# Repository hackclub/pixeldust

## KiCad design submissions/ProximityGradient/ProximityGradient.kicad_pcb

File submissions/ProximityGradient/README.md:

---
name: "Youssef Mostafa"
slack_id: "U086LEPFDC5"
github_handle: "@yousseftechdev"
tutorial: [default guide](https://pixeldust.hackclub.com/guidelines)
wokwi: [WOKWI PROJECT](https://wokwi.com/projects/426893863510548481)
---

# ProximityGradient

Wokwi link: [https://wokwi.com/projects/426893863510548481](https://wokwi.com/projects/426893863510548481)

<!-- Uncomment the line below if you need a soldering iron -->
<!-- ⚠️ I would like to [reason for iron], so I would need a soldering iron. -->

Describe your board in 2-3 sentences. What are you making? What will it do? Please add a lot of pictures here!!

**Simple NeoMatrix connected to an UltraSonic distance sensor (Provided by me) that shows a circle that grows in proportion to the distance, the closer and object gets to the sensor, the bigger the circle gets and the red-er it gets.**

A simplified BOM table
(pls include rough pricing of any extra components you're using)

<!-- Example: -->

| Comment           | Footprint                                      | Quantity | LCSC     | Cost   |
|-------------------|------------------------------------------------|----------|----------|--------|
| 100uF             | C_1206_3216Metric_Pad1.33x1.80mm_HandSolder    | 1        | C15008   | 0.0682$|
| 4.7nF             | C_0402_1005Metric_Pad0.74x0.62mm_HandSolder    | 8        | C1538    | 0.0011$|
| 5.1Kohm           | Resistor_SMD:R_1206_3216Metric_Pad1.30x1.75mm_HandSolder| 2        | 0805W8F5101T5E    | $0.0018|
| WS2812B           | LED_WS2812B_PLCC4_5.0x5.0mm_P3.2mm             | 49       | XL-5050RGBC-WS2812B    | $0.0489|
| XIAO-RP2040-DIP   | XIAO-RP2040-DIP                                | 1        |          |

Tell us a little bit about your design process. What were some challenges? What helped?
The biggest challenge I had to face was learning how to use KiCad, thankfully the slack members helped me a lot, I had to change the design a lot because a slack member would point out an error in my board.

Some images of your design (make sure to include both the PCB and Schematic!):

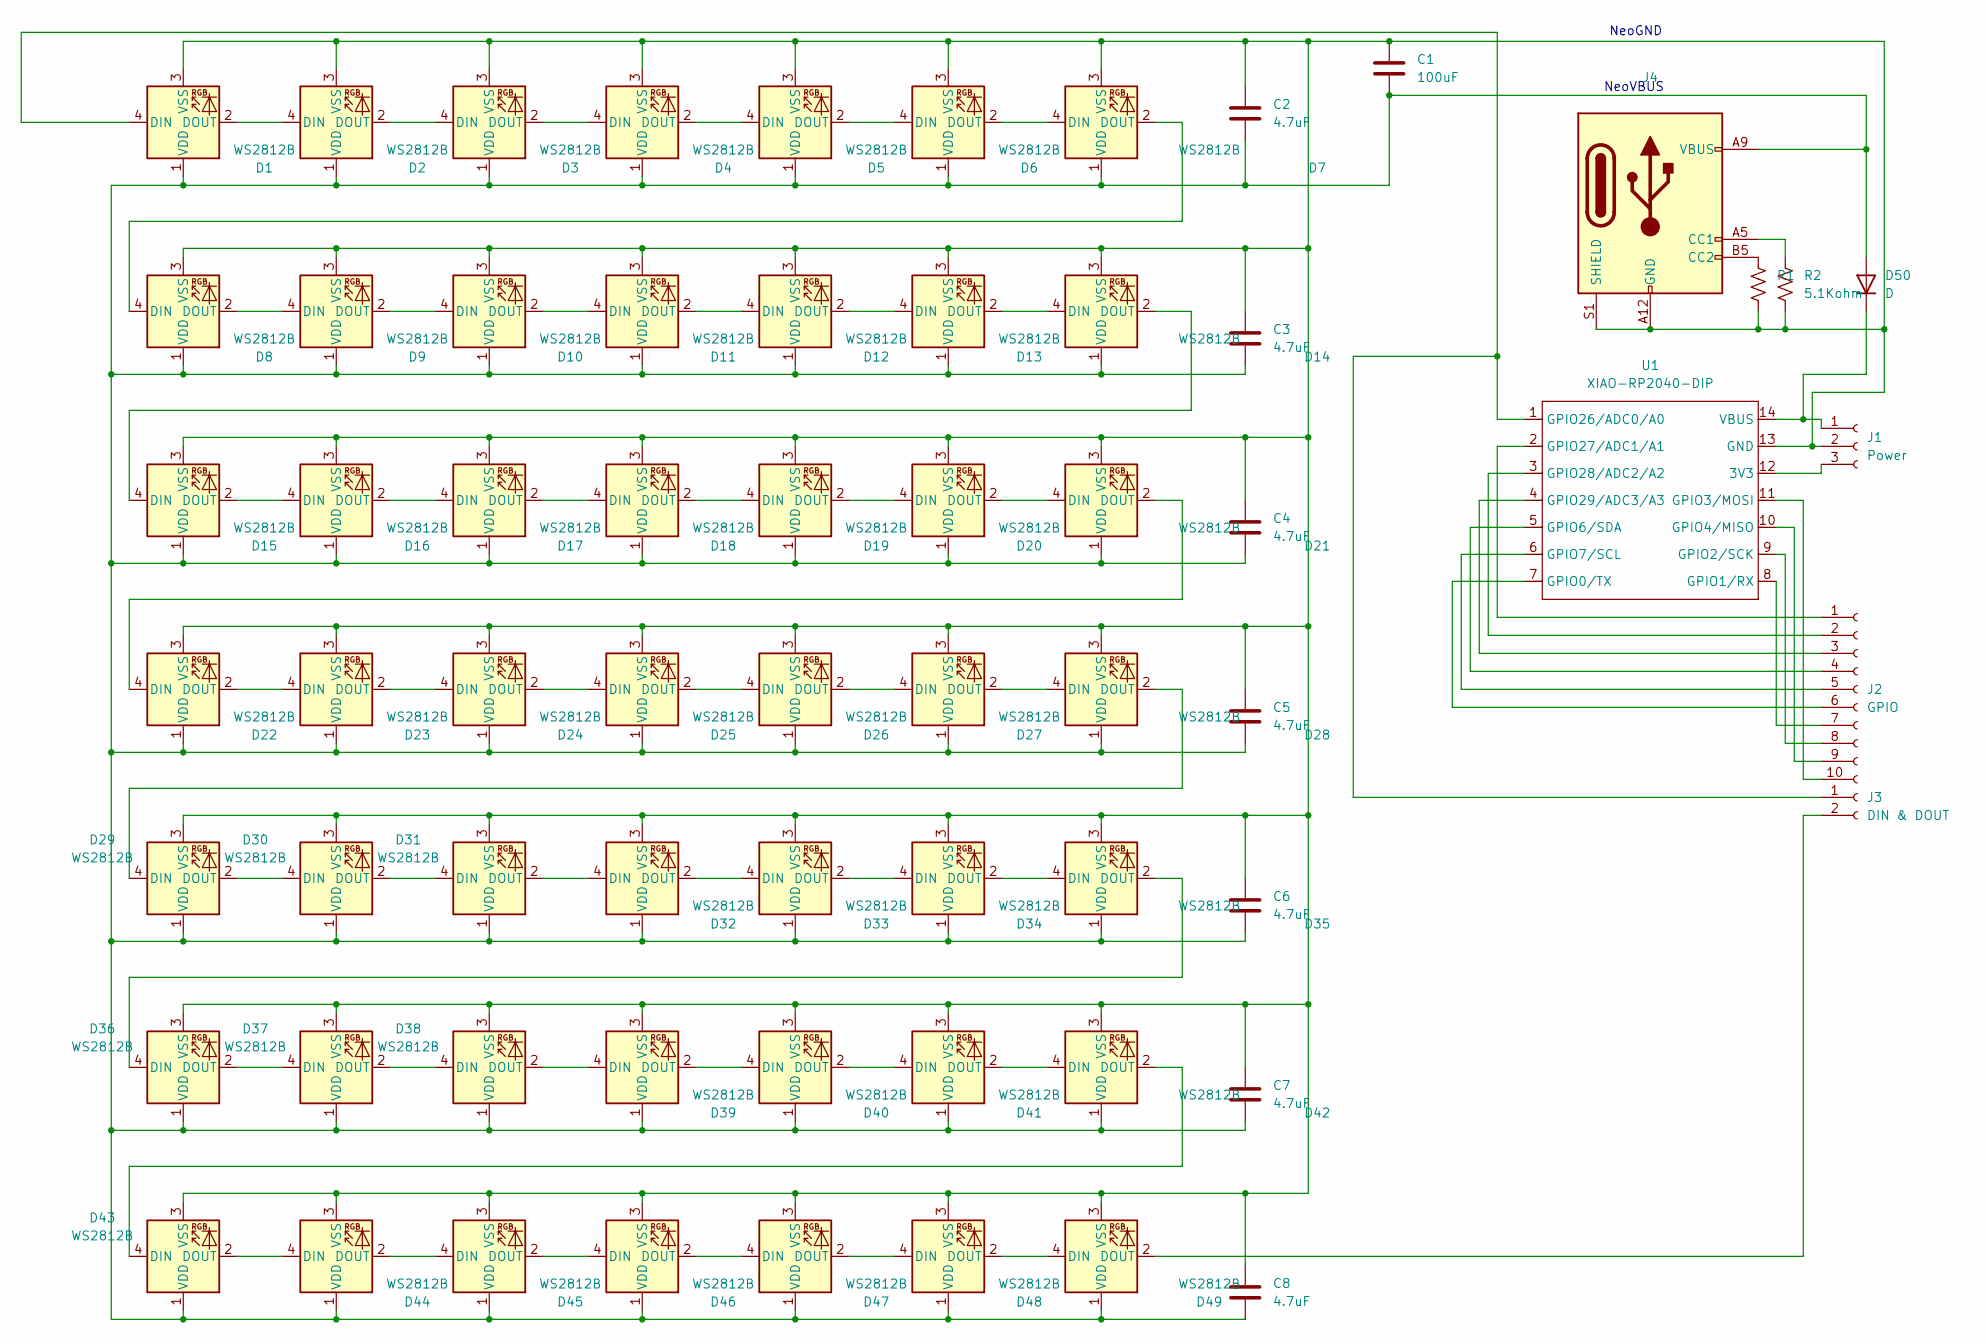
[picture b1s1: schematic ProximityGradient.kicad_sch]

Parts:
C1: 100uF; C_1206_3216Metric_Pad1.33x1.80mm_HandSolder
C2, C3, C4, C5, C6, C7, C8: 4.7uF; C_0805_2012Metric_Pad1.18x1.45mm_HandSolder
D1, D2, D3, D4, D5, D6, D7, D8, D9, D10, D11, D12, D13, D14, D15, D16, D17, D18, D19, D20, D21, D22, D23, D24, D25, D26, D27, D28, D29, D30, D31, D32, D33, D34, D35, D36, D37, D38, D39, D40, D41, D42, D43, D44, D45, D46, D47, D48, D49: WS2812B; LED_WS2812B_PLCC4_5.0x5.0mm_P3.2mm
D50: D; D_0805_2012Metric_Pad1.15x1.40mm_HandSolder
J1: Power; PinSocket_1x03_P2.00mm_Vertical
J2: GPIO; PinSocket_1x10_P2.00mm_Vertical
J3: DIN & DOUT; PinSocket_1x02_P2.00mm_Vertical
J4: USB_C_Receptacle_PowerOnly_6P; USB_C_Receptacle_GCT_USB4125-xx-x_6P_TopMnt_Horizontal
R1: R_US; R_1206_3216Metric_Pad1.30x1.75mm_HandSolder
R2: 5.1Kohm; R_1206_3216Metric_Pad1.30x1.75mm_HandSolder
U1: XIAO-RP2040-DIP

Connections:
unnamed: D1.4 (DIN), J3.1, U1.1 (GPIO26/ADC0/A0)
unnamed: D1.2 (DOUT), D2.4 (DIN)
unnamed: C1.2, C2.2, C3.2, C4.2, C5.2, C6.2, C7.2, C8.2, D1.1 (VDD), D2.1 (VDD), D3.1 (VDD), D4.1 (VDD), D5.1 (VDD), D6.1 (VDD), D7.1 (VDD), D8.1 (VDD), D9.1 (VDD), D10.1 (VDD), D11.1 (VDD), D12.1 (VDD), D13.1 (VDD), D14.1 (VDD), D15.1 (VDD), D16.1 (VDD), D17.1 (VDD), D18.1 (VDD), D19.1 (VDD), D20.1 (VDD), D21.1 (VDD), D22.1 (VDD), D23.1 (VDD), D24.1 (VDD), D25.1 (VDD), D26.1 (VDD), D27.1 (VDD), D28.1 (VDD), D29.1 (VDD), D30.1 (VDD), D31.1 (VDD), D32.1 (VDD), D33.1 (VDD), D34.1 (VDD), D35.1 (VDD), D36.1 (VDD), D37.1 (VDD), D38.1 (VDD), D39.1 (VDD), D40.1 (VDD), D41.1 (VDD), D42.1 (VDD), D43.1 (VDD), D44.1 (VDD), D45.1 (VDD), D46.1 (VDD), D47.1 (VDD), D48.1 (VDD), D49.1 (VDD), D50.2 (A), J4.A9 (VBUS), J4.B9 (VBUS)
unnamed: C1.1, C2.1, C3.1, C4.1, C5.1, C6.1, C7.1, C8.1, D1.3 (VSS), D2.3 (VSS), D3.3 (VSS), D4.3 (VSS), D5.3 (VSS), D6.3 (VSS), D7.3 (VSS), D8.3 (VSS), D9.3 (VSS), D10.3 (VSS), D11.3 (VSS), D12.3 (VSS), D13.3 (VSS), D14.3 (VSS), D15.3 (VSS), D16.3 (VSS), D17.3 (VSS), D18.3 (VSS), D19.3 (VSS), D20.3 (VSS), D21.3 (VSS), D22.3 (VSS), D23.3 (VSS), D24.3 (VSS), D25.3 (VSS), D26.3 (VSS), D27.3 (VSS), D28.3 (VSS), D29.3 (VSS), D30.3 (VSS), D31.3 (VSS), D32.3 (VSS), D33.3 (VSS), D34.3 (VSS), D35.3 (VSS), D36.3 (VSS), D37.3 (VSS), D38.3 (VSS), D39.3 (VSS), D40.3 (VSS), D41.3 (VSS), D42.3 (VSS), D43.3 (VSS), D44.3 (VSS), D45.3 (VSS), D46.3 (VSS), D47.3 (VSS), D48.3 (VSS), D49.3 (VSS), J1.2, J4.A12 (GND), J4.B12 (GND), J4.S1 (SHIELD), R1.2, R2.2, U1.13 (GND)
unnamed: D2.2 (DOUT), D3.4 (DIN)
unnamed: D3.2 (DOUT), D4.4 (DIN)
unnamed: D4.2 (DOUT), D5.4 (DIN)
unnamed: D5.2 (DOUT), D6.4 (DIN)
unnamed: D6.2 (DOUT), D7.4 (DIN)
unnamed: D7.2 (DOUT), D8.4 (DIN)
unnamed: D8.2 (DOUT), D9.4 (DIN)
unnamed: D9.2 (DOUT), D10.4 (DIN)
unnamed: D10.2 (DOUT), D11.4 (DIN)
unnamed: D11.2 (DOUT), D12.4 (DIN)
unnamed: D12.2 (DOUT), D13.4 (DIN)
unnamed: D13.2 (DOUT), D14.4 (DIN)
unnamed: D14.2 (DOUT), D15.4 (DIN)
unnamed: D15.2 (DOUT), D16.4 (DIN)
unnamed: D16.2 (DOUT), D17.4 (DIN)
unnamed: D17.2 (DOUT), D18.4 (DIN)
unnamed: D18.2 (DOUT), D19.4 (DIN)
unnamed: D19.2 (DOUT), D20.4 (DIN)
unnamed: D20.2 (DOUT), D21.4 (DIN)
unnamed: D21.2 (DOUT), D22.4 (DIN)
unnamed: D22.2 (DOUT), D23.4 (DIN)
unnamed: D23.2 (DOUT), D24.4 (DIN)
unnamed: D24.2 (DOUT), D25.4 (DIN)
unnamed: D25.2 (DOUT), D26.4 (DIN)
unnamed: D26.2 (DOUT), D27.4 (DIN)
unnamed: D27.2 (DOUT), D28.4 (DIN)
unnamed: D28.2 (DOUT), D29.4 (DIN)
unnamed: D29.2 (DOUT), D30.4 (DIN)
unnamed: D30.2 (DOUT), D31.4 (DIN)
unnamed: D31.2 (DOUT), D32.4 (DIN)
unnamed: D32.2 (DOUT), D33.4 (DIN)
unnamed: D33.2 (DOUT), D34.4 (DIN)
unnamed: D34.2 (DOUT), D35.4 (DIN)
unnamed: D35.2 (DOUT), D36.4 (DIN)
unnamed: D36.2 (DOUT), D37.4 (DIN)
unnamed: D37.2 (DOUT), D38.4 (DIN)
unnamed: D38.2 (DOUT), D39.4 (DIN)
unnamed: D39.2 (DOUT), D40.4 (DIN)
unnamed: D40.2 (DOUT), D41.4 (DIN)
unnamed: D41.2 (DOUT), D42.4 (DIN)
unnamed: D42.2 (DOUT), D43.4 (DIN)
unnamed: D43.2 (DOUT), D44.4 (DIN)
unnamed: D44.2 (DOUT), D45.4 (DIN)
unnamed: D45.2 (DOUT), D46.4 (DIN)
unnamed: D46.2 (DOUT), D47.4 (DIN)
unnamed: D47.2 (DOUT), D48.4 (DIN)
unnamed: D48.2 (DOUT), D49.4 (DIN)
unnamed: D49.2 (DOUT), J3.2
unnamed: D50.1 (K), J1.1, U1.14 (VBUS)
unnamed: J1.3, U1.12 (3V3)
unnamed: J2.1, U1.2 (GPIO27/ADC1/A1)
unnamed: J2.2, U1.3 (GPIO28/ADC2/A2)
unnamed: J2.3, U1.4 (GPIO29/ADC3/A3)
unnamed: J2.4, U1.5 (GPIO6/SDA)
unnamed: J2.5, U1.6 (GPIO7/SCL)
unnamed: J2.6, U1.7 (GPIO0/TX)
unnamed: J2.7, U1.8 (GPIO1/RX)
unnamed: J2.8, U1.9 (GPIO2/SCK)
unnamed: J2.9, U1.10 (GPIO4/MISO)
unnamed: J2.10, U1.11 (GPIO3/MOSI)
unnamed: J4.A5 (CC1), R2.1
unnamed: J4.B5 (CC2), R1.1

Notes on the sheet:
NeoVBUS
NeoGND

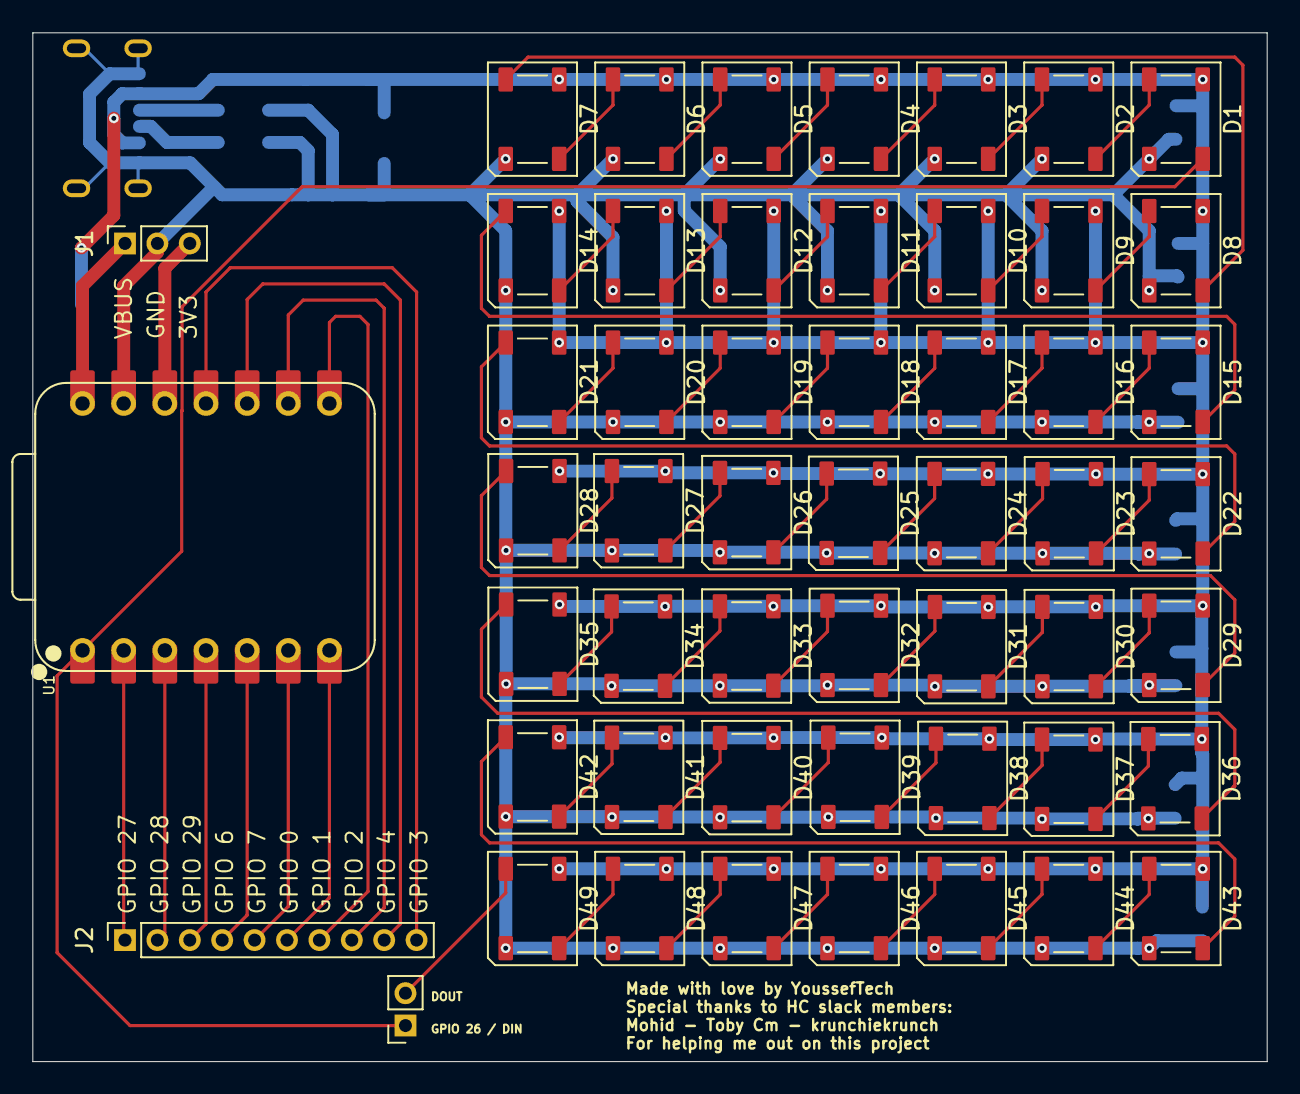
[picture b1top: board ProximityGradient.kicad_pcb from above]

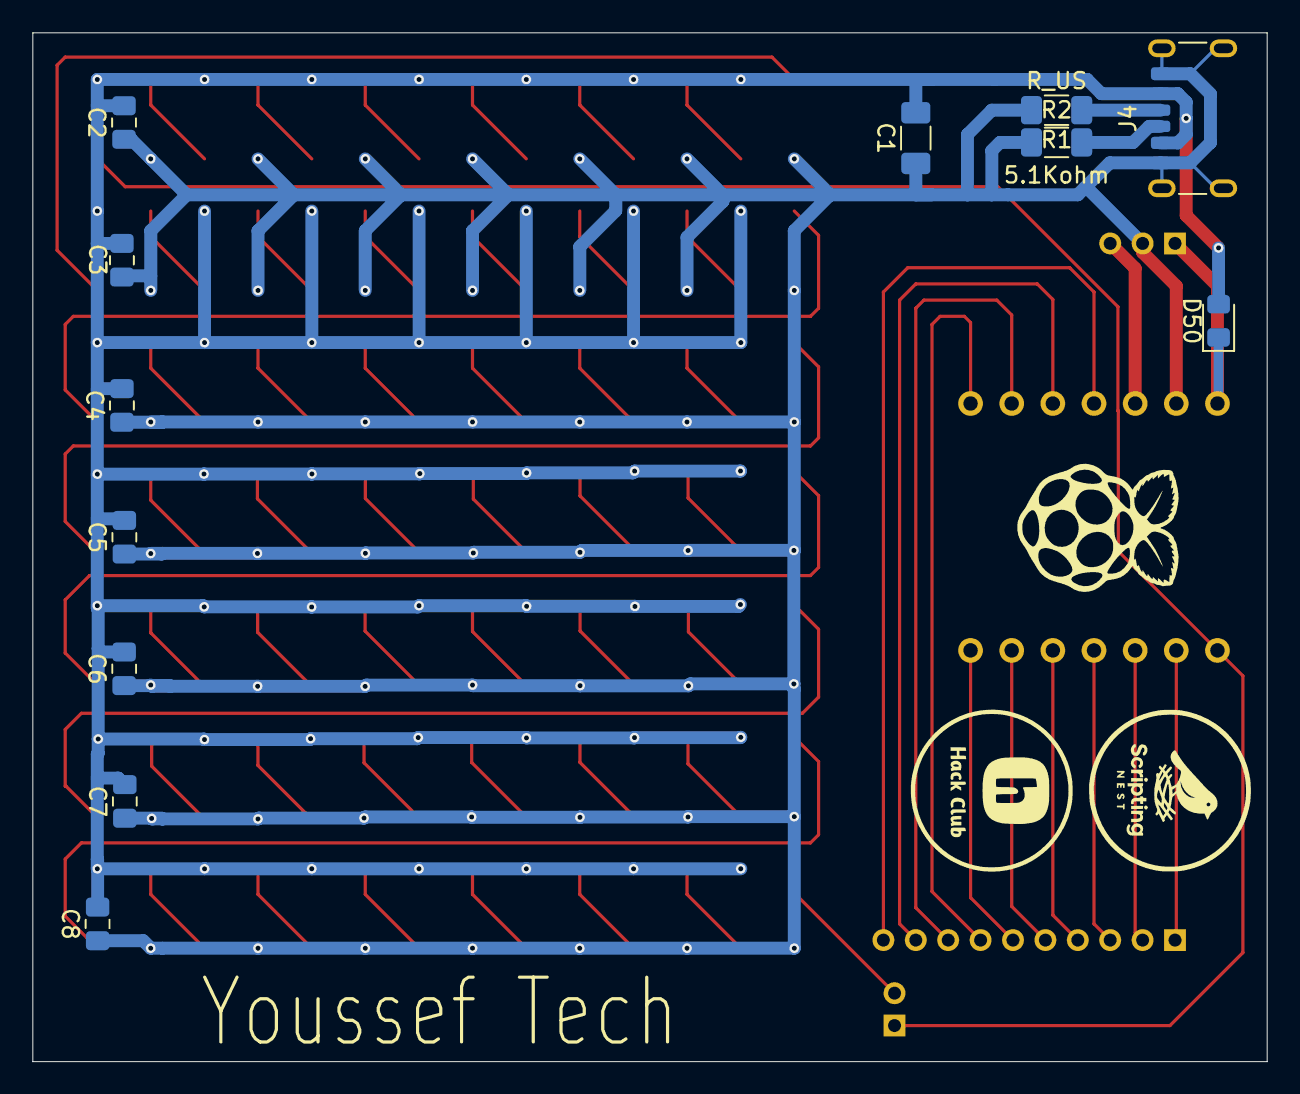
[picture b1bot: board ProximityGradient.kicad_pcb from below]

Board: 2 copper layers, 76.2 x 63.5 mm, 65 parts (12 on the bottom side), 66 nets.

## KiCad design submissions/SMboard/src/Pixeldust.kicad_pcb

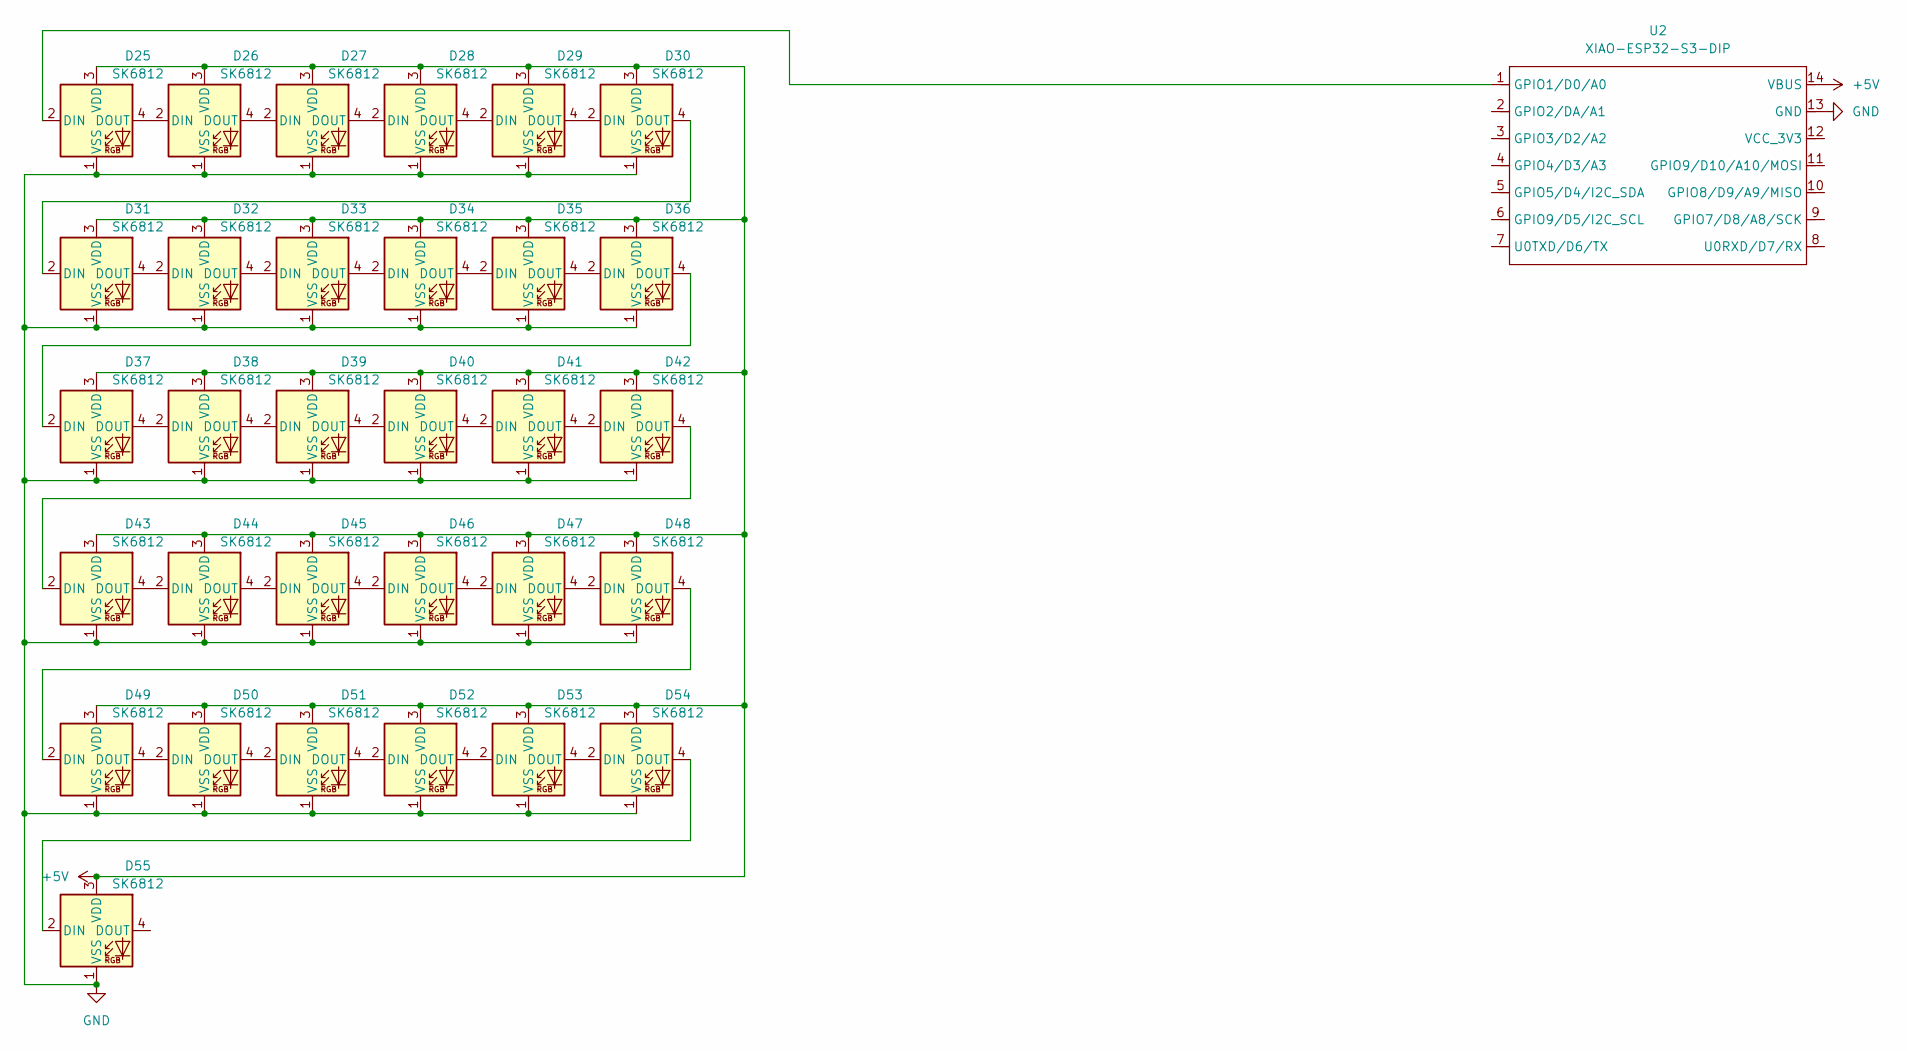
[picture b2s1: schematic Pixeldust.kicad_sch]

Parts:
D25, D26, D27, D28, D29, D30, D31, D32, D33, D34, D35, D36, D37, D38, D39, D40, D41, D42, D43, D44, D45, D46, D47, D48, D49, D50, D51, D52, D53, D54, D55: SK6812; LED_SK6812_PLCC4_5.0x5.0mm_P3.2mm
U2: XIAO-ESP32-S3-DIP; XIAO-ESP32S3-DIP

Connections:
+5V: D25.3 (VDD), D26.3 (VDD), D27.3 (VDD), D28.3 (VDD), D29.3 (VDD), D30.3 (VDD), D31.3 (VDD), D32.3 (VDD), D33.3 (VDD), D34.3 (VDD), D35.3 (VDD), D36.3 (VDD), D37.3 (VDD), D38.3 (VDD), D39.3 (VDD), D40.3 (VDD), D41.3 (VDD), D42.3 (VDD), D43.3 (VDD), D44.3 (VDD), D45.3 (VDD), D46.3 (VDD), D47.3 (VDD), D48.3 (VDD), D49.3 (VDD), D50.3 (VDD), D51.3 (VDD), D52.3 (VDD), D53.3 (VDD), D54.3 (VDD), D55.3 (VDD), U2.14 (VBUS)
GND: D25.1 (VSS), D26.1 (VSS), D27.1 (VSS), D28.1 (VSS), D29.1 (VSS), D30.1 (VSS), D31.1 (VSS), D32.1 (VSS), D33.1 (VSS), D34.1 (VSS), D35.1 (VSS), D36.1 (VSS), D37.1 (VSS), D38.1 (VSS), D39.1 (VSS), D40.1 (VSS), D41.1 (VSS), D42.1 (VSS), D43.1 (VSS), D44.1 (VSS), D45.1 (VSS), D46.1 (VSS), D47.1 (VSS), D48.1 (VSS), D49.1 (VSS), D50.1 (VSS), D51.1 (VSS), D52.1 (VSS), D53.1 (VSS), D54.1 (VSS), D55.1 (VSS), U2.13 (GND)
unnamed: D25.2 (DIN), U2.1 (GPIO1/D0/A0)
unnamed: D25.4 (DOUT), D26.2 (DIN)
unnamed: D26.4 (DOUT), D27.2 (DIN)
unnamed: D27.4 (DOUT), D28.2 (DIN)
unnamed: D28.4 (DOUT), D29.2 (DIN)
unnamed: D29.4 (DOUT), D30.2 (DIN)
unnamed: D30.4 (DOUT), D31.2 (DIN)
unnamed: D31.4 (DOUT), D32.2 (DIN)
unnamed: D32.4 (DOUT), D33.2 (DIN)
unnamed: D33.4 (DOUT), D34.2 (DIN)
unnamed: D34.4 (DOUT), D35.2 (DIN)
unnamed: D35.4 (DOUT), D36.2 (DIN)
unnamed: D36.4 (DOUT), D37.2 (DIN)
unnamed: D37.4 (DOUT), D38.2 (DIN)
unnamed: D38.4 (DOUT), D39.2 (DIN)
unnamed: D39.4 (DOUT), D40.2 (DIN)
unnamed: D40.4 (DOUT), D41.2 (DIN)
unnamed: D41.4 (DOUT), D42.2 (DIN)
unnamed: D42.4 (DOUT), D43.2 (DIN)
unnamed: D43.4 (DOUT), D44.2 (DIN)
unnamed: D44.4 (DOUT), D45.2 (DIN)
unnamed: D45.4 (DOUT), D46.2 (DIN)
unnamed: D46.4 (DOUT), D47.2 (DIN)
unnamed: D47.4 (DOUT), D48.2 (DIN)
unnamed: D48.4 (DOUT), D49.2 (DIN)
unnamed: D49.4 (DOUT), D50.2 (DIN)
unnamed: D50.4 (DOUT), D51.2 (DIN)
unnamed: D51.4 (DOUT), D52.2 (DIN)
unnamed: D52.4 (DOUT), D53.2 (DIN)
unnamed: D53.4 (DOUT), D54.2 (DIN)
unnamed: D54.4 (DOUT), D55.2 (DIN)

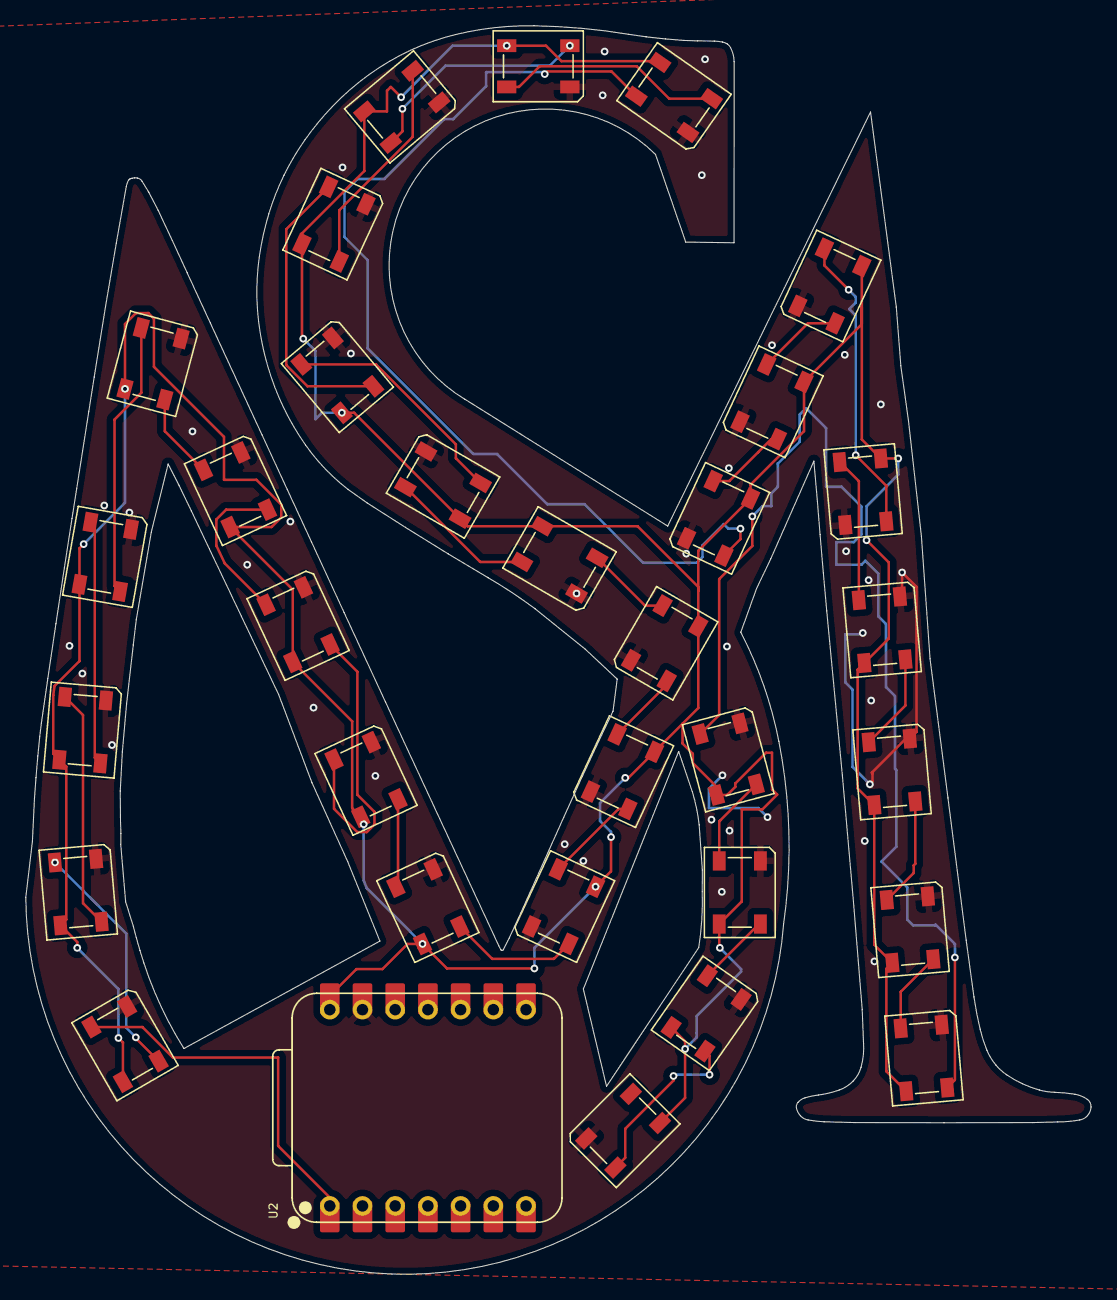
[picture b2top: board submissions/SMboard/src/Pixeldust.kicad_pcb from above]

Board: 2 copper layers, 82.7 x 96.9 mm, 32 parts (0 on the bottom side), 33 nets.

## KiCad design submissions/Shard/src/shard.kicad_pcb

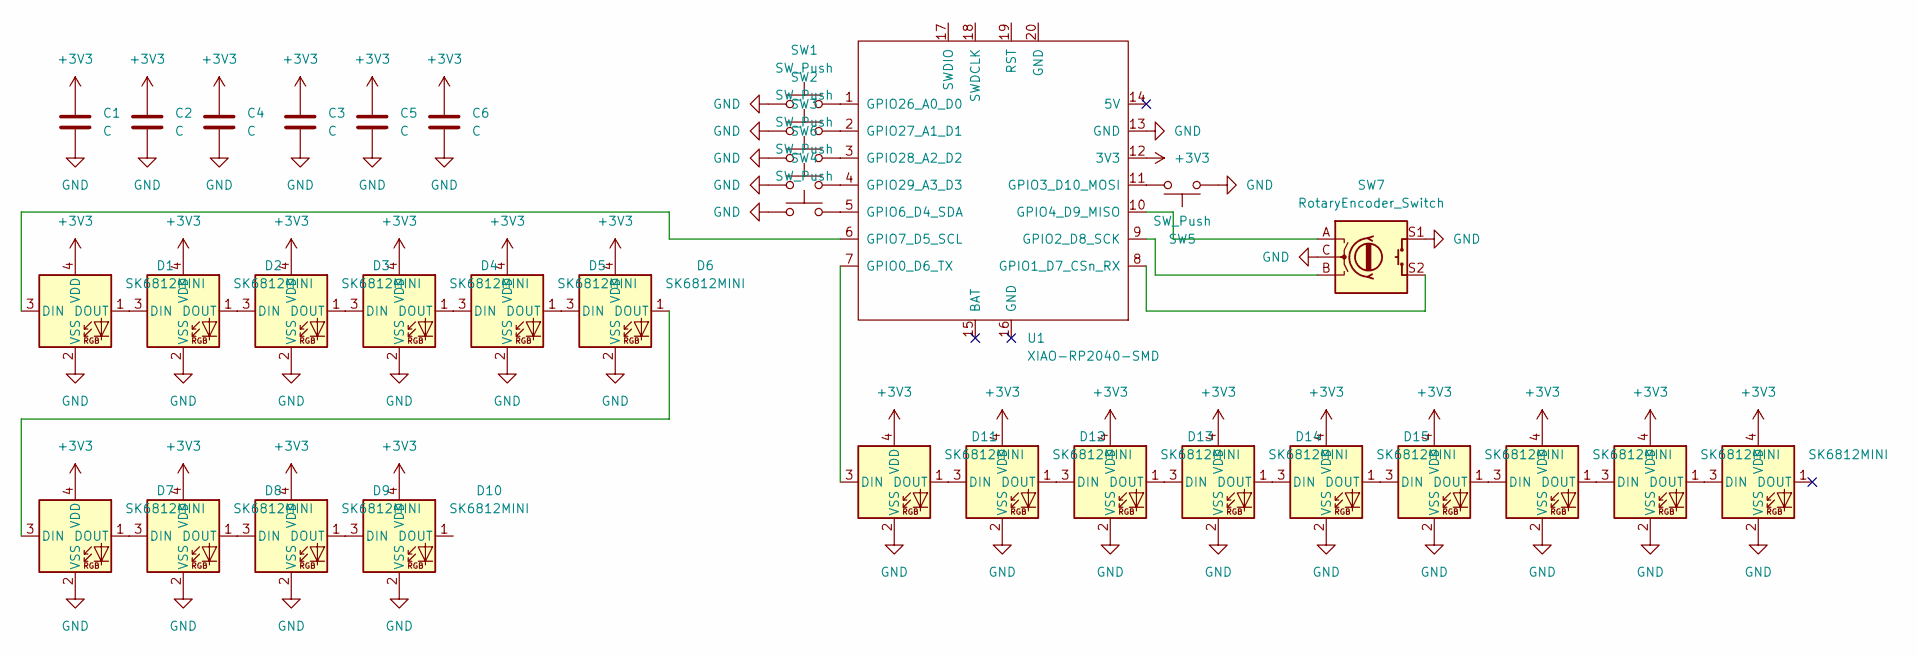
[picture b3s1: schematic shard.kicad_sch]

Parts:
C1, C2, C3, C4, C5, C6: C; C_0805_2012Metric_Pad1.18x1.45mm_HandSolder
D1, D2, D3, D4, D5, D6, D7, D8, D9, D10, D11, D12, D13, D14, D15, D16, D17, D18, D19: SK6812MINI; SK6812MINI-E
SW1, SW2, SW3, SW4, SW5, SW6: SW_Push; SW_Cherry_MX_1.00u_PCB
SW7: RotaryEncoder_Switch; RotaryEncoder_Alps_EC11E-Switch_Vertical_H20mm_MountingHoles
U1: XIAO-RP2040-SMD

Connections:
+3V3: C1.1, C2.1, C3.1, C4.1, C5.1, C6.1, D1.4 (VDD), D2.4 (VDD), D3.4 (VDD), D4.4 (VDD), D5.4 (VDD), D6.4 (VDD), D7.4 (VDD), D8.4 (VDD), D9.4 (VDD), D10.4 (VDD), D11.4 (VDD), D12.4 (VDD), D13.4 (VDD), D14.4 (VDD), D15.4 (VDD), D16.4 (VDD), D17.4 (VDD), D18.4 (VDD), D19.4 (VDD), U1.12 (3V3)
GND: C1.2, C2.2, C3.2, C4.2, C5.2, C6.2, D1.2 (VSS), D2.2 (VSS), D3.2 (VSS), D4.2 (VSS), D5.2 (VSS), D6.2 (VSS), D7.2 (VSS), D8.2 (VSS), D9.2 (VSS), D10.2 (VSS), D11.2 (VSS), D12.2 (VSS), D13.2 (VSS), D14.2 (VSS), D15.2 (VSS), D16.2 (VSS), D17.2 (VSS), D18.2 (VSS), D19.2 (VSS), SW1.1, SW2.1, SW3.1, SW4.1, SW5.2, SW6.2, SW7.C, SW7.S1, U1.13 (GND)
unnamed: D1.3 (DIN), U1.6 (GPIO7_D5_SCL)
unnamed: D1.1 (DOUT), D2.3 (DIN)
unnamed: D2.1 (DOUT), D3.3 (DIN)
unnamed: D3.1 (DOUT), D4.3 (DIN)
unnamed: D4.1 (DOUT), D5.3 (DIN)
unnamed: D5.1 (DOUT), D6.3 (DIN)
unnamed: D6.1 (DOUT), D7.3 (DIN)
unnamed: D7.1 (DOUT), D8.3 (DIN)
unnamed: D8.1 (DOUT), D9.3 (DIN)
unnamed: D9.1 (DOUT), D10.3 (DIN)
unnamed: D11.3 (DIN), U1.7 (GPIO0_D6_TX)
unnamed: D11.1 (DOUT), D12.3 (DIN)
unnamed: D12.1 (DOUT), D13.3 (DIN)
unnamed: D13.1 (DOUT), D14.3 (DIN)
unnamed: D14.1 (DOUT), D15.3 (DIN)
unnamed: D15.1 (DOUT), D16.3 (DIN)
unnamed: D16.1 (DOUT), D17.3 (DIN)
unnamed: D17.1 (DOUT), D18.3 (DIN)
unnamed: D18.1 (DOUT), D19.3 (DIN)
unnamed: SW7.S2, U1.8 (GPIO1_D7_CSn_RX)
unnamed: SW7.B, U1.9 (GPIO2_D8_SCK)
unnamed: SW5.1, U1.11 (GPIO3_D10_MOSI)
unnamed: SW7.A, U1.10 (GPIO4_D9_MISO)
unnamed: SW4.2, U1.5 (GPIO6_D4_SDA)
unnamed: SW1.2, U1.1 (GPIO26_A0_D0)
unnamed: SW2.2, U1.2 (GPIO27_A1_D1)
unnamed: SW3.2, U1.3 (GPIO28_A2_D2)
unnamed: SW6.1, U1.4 (GPIO29_A3_D3)

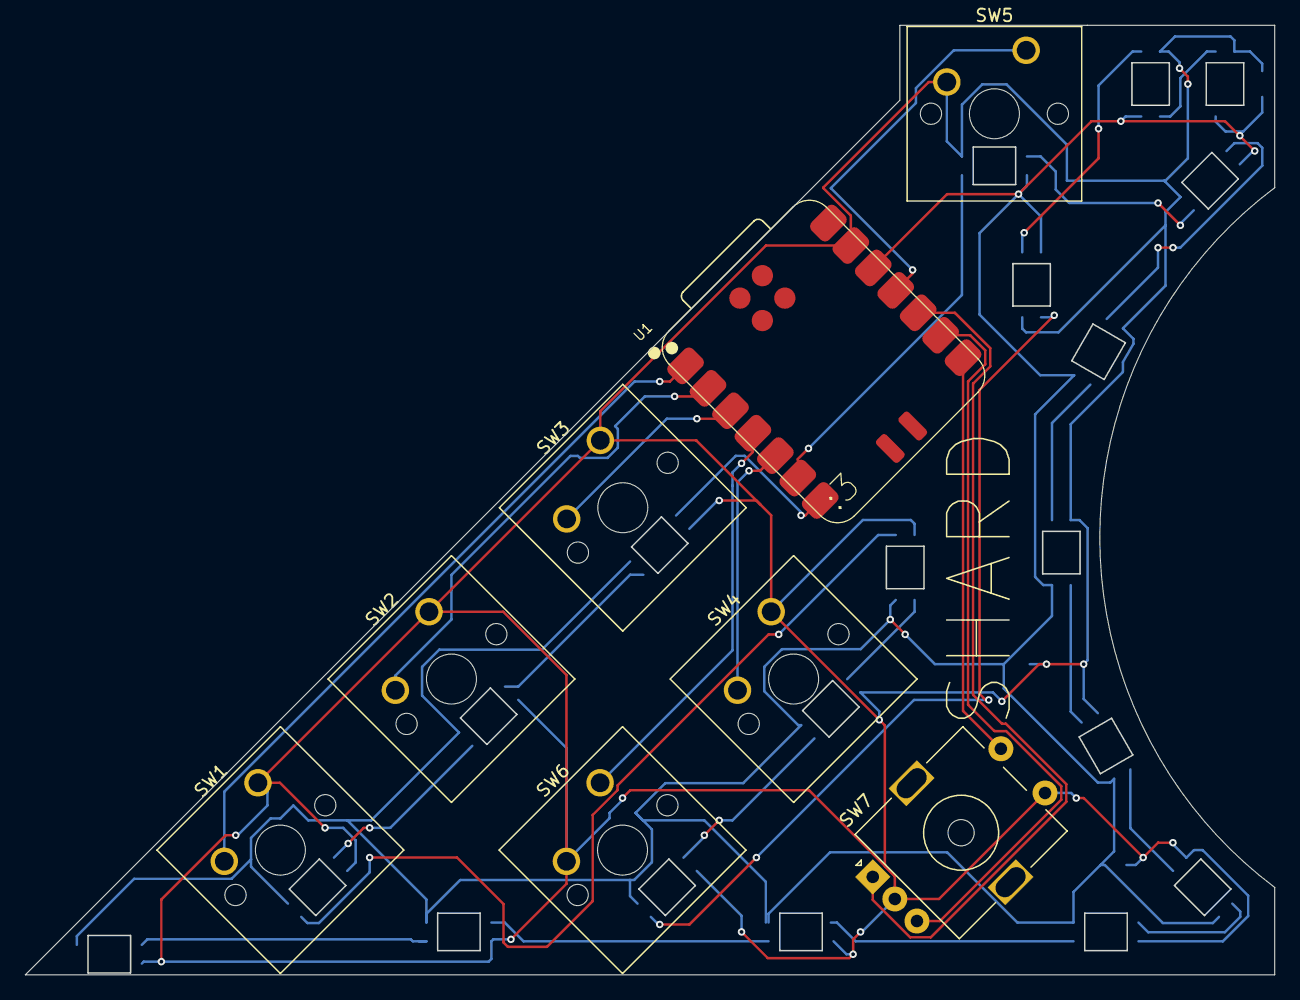
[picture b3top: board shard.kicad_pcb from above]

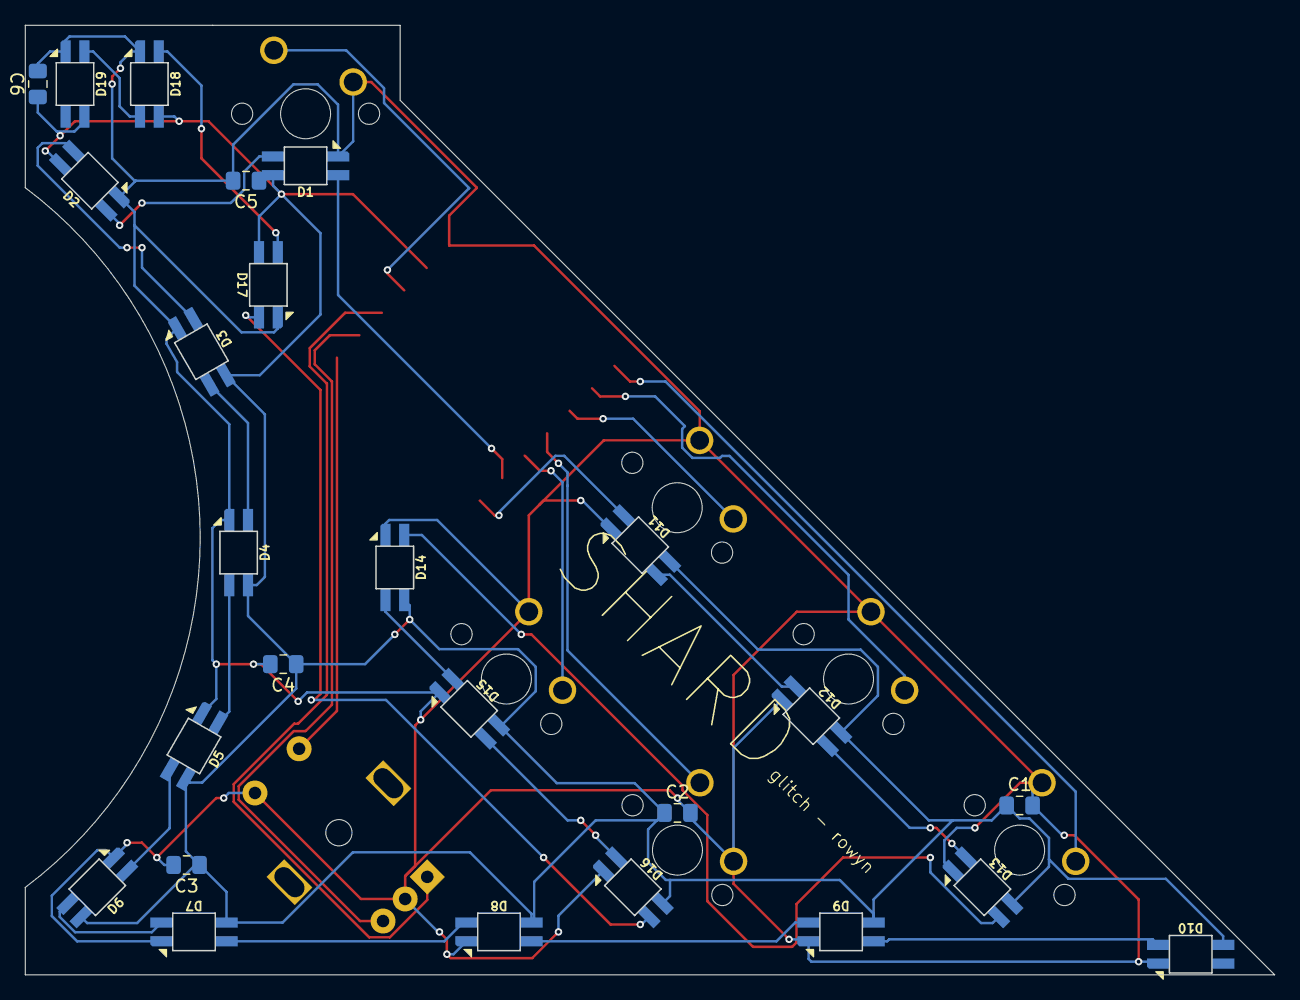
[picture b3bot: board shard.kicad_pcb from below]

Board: 2 copper layers, 100.0 x 76.0 mm, 33 parts (25 on the bottom side), 30 nets.

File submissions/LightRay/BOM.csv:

"Reference","Value","Footprint","Datasheet","Qty","DNP","Exclude from BOM","Exclude from Board"
"C1","100uF","Capacitor_SMD:C_1210_3225Metric_Pad1.33x2.70mm_HandSolder","~","1","","",""
"C2,C3,C4","4.7nF","Capacitor_SMD:C_1206_3216Metric_Pad1.33x1.80mm_HandSolder","~","3","","",""
"D1,D2,D3,D4,D5,D6,D7,D8,D9,D10,D11,D12,D13,D14,D15","WS2812B","LED_SMD:LED_WS2812B_PLCC4_5.0x5.0mm_P3.2mm","https://cdn-shop.adafruit.com/datasheets/WS2812B.pdf","15","","",""
"SW1","RotaryEncoder_Switch","Rotary_Encoder:RotaryEncoder_Alps_EC11E-Switch_Vertical_H20mm","~","1","","",""
"SW2,SW3","SW_Push","Button_Switch_Keyboard:SW_Cherry_MX_1.00u_PCB","~","2","","",""
"U1","XIAO-RP2040-SMD","OPL:XIAO-RP2040-SMD","","1","","",""

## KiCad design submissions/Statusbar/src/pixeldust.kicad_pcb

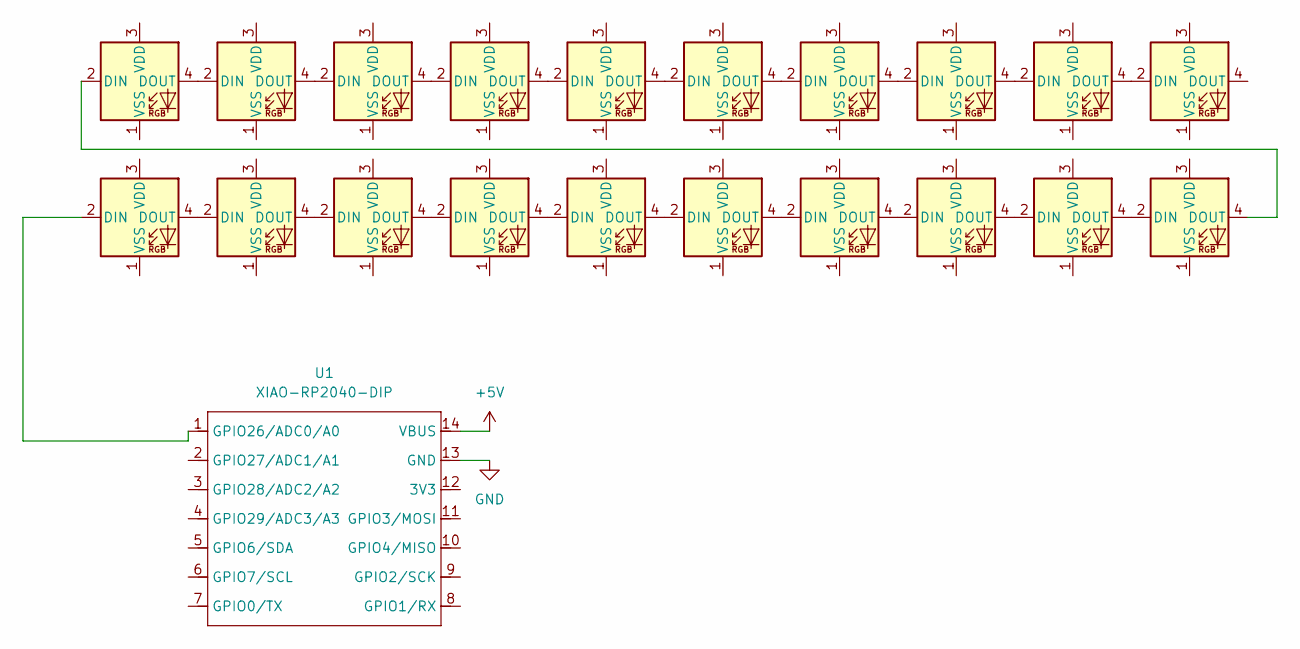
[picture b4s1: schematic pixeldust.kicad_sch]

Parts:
D1, D2, D3, D4, D5, D6, D7, D8, D9, D10, D11, D12, D13, D14, D15, D16, D17, D18, D19, D20: SK6812; LED_SK6812_PLCC4_5.0x5.0mm_P3.2mm
U1: XIAO-RP2040-DIP

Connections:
+5V: U1.14 (VBUS)
GND: U1.13 (GND)
unnamed: D1.2 (DIN), U1.1 (GPIO26/ADC0/A0)
unnamed: D1.4 (DOUT), D2.2 (DIN)
unnamed: D2.4 (DOUT), D3.2 (DIN)
unnamed: D3.4 (DOUT), D4.2 (DIN)
unnamed: D4.4 (DOUT), D5.2 (DIN)
unnamed: D5.4 (DOUT), D6.2 (DIN)
unnamed: D6.4 (DOUT), D7.2 (DIN)
unnamed: D7.4 (DOUT), D8.2 (DIN)
unnamed: D8.4 (DOUT), D9.2 (DIN)
unnamed: D9.4 (DOUT), D10.2 (DIN)
unnamed: D10.4 (DOUT), D11.2 (DIN)
unnamed: D11.4 (DOUT), D12.2 (DIN)
unnamed: D12.4 (DOUT), D13.2 (DIN)
unnamed: D13.4 (DOUT), D14.2 (DIN)
unnamed: D14.4 (DOUT), D15.2 (DIN)
unnamed: D15.4 (DOUT), D16.2 (DIN)
unnamed: D16.4 (DOUT), D17.2 (DIN)
unnamed: D17.4 (DOUT), D18.2 (DIN)
unnamed: D18.4 (DOUT), D19.2 (DIN)
unnamed: D19.4 (DOUT), D20.2 (DIN)

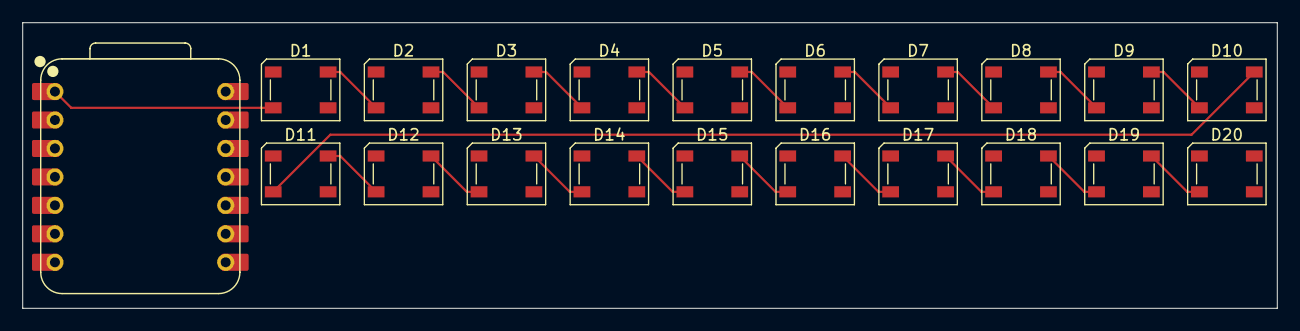
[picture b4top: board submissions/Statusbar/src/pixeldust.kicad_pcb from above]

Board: 2 copper layers, 112.0 x 25.5 mm, 21 parts (0 on the bottom side), 20 nets.

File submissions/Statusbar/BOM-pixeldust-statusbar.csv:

"Reference","Value","Datasheet","Footprint","Qty","DNP"
"D1,D2,D3,D4,D5,D6,D7,D8,D9,D10,D11,D12,D13,D14,D15,D16,D17,D18,D19,D20","SK6812","https://cdn-shop.adafruit.com/product-files/1138/SK6812+LED+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","LED_SMD:LED_SK6812_PLCC4_5.0x5.0mm_P3.2mm","20",""
"U1","XIAO-RP2040-DIP","","Custom:XIAO-RP2040-DIP","1",""
